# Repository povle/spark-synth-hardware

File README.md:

[![CC BY-NC-SA 4.0][cc-by-nc-sa-shield]][cc-by-nc-sa]

This work is licensed under a
[Creative Commons Attribution-NonCommercial-ShareAlike 4.0 International License][cc-by-nc-sa].

[![CC BY-NC-SA 4.0][cc-by-nc-sa-image]][cc-by-nc-sa]

[cc-by-nc-sa]: http://creativecommons.org/licenses/by-nc-sa/4.0/
[cc-by-nc-sa-image]: https://licensebuttons.net/l/by-nc-sa/4.0/88x31.png
[cc-by-nc-sa-shield]: https://img.shields.io/badge/License-CC%20BY--NC--SA%204.0-lightgrey.svg

# Spark Synth - Hardware
This repo is intended to host the hardware files and assembly information for [Spark](https://github.com/povle/spark-synth) - an open-source portable ESP32-based synth.

Important disclaimer: currently, this project is a prototype. If you really want to assemble it yourself, be prepared for a lot of drilling, sanding, double-sided-taping, soldering tiny wires and figuring stuff out on your own. You can contact [me on Reddit](https://www.reddit.com/user/Pashog/) and I might help if I have the time for that, but no guarantees here.

Moving forward I'm planning to design an easier to assemble V2 with everything mounted on custom PCBs, but I can't provide any timeline on that.

Feel free to modify and improve the design, but respect the licensing.

## Electronics - Bill of Materials
|   Component                                                                 | Function                         | **Comments**                                                                                                                                                                                                                                                                                                      |
|-----------------------------------------------------------------------------|----------------------------------|-------------------------------------------------------------------------------------------------------------------------------------------------------------------------------------------------------------------------------------------------------------------------------------------------------------------|
| ESP-32 S3 N16R8                                                             | Microcontroller                  | I've used some no-name devboard marked "S3 AI". Note the "N16R8" - the project does need a lot of PSRAM.                                                                                                                                                                                                          |
| PCM 5102A                                                                   | DAC                              |                                                                                                                                                                                                                                                                                                                   |
| PAM8403                                                                     | Amp                              |                                                                                                                                                                                                                                                                                                                   |
| RV09 (10 kOhm) (x16)                                                        | Potentiometers                   | Not sure what the exact model is, but mine are vertical with a plastic 12 mm long knurled shaft.                                                                                                                                                                                                                  |
| YANJUXING 4020 4 Ohm 3W                                                     | Speaker                          | Found it on Aliexpress. It's rectangular, 40mm x 20 mm, 14.3 mm tall. The dimensions are critical, it's a pretty tight fit.                                                                                                                                                                                       |
| Adafruit USB-C breakout board                                               | USB-C                            | Any peripheral breakout board you can find that has both power and data will do. I've used a copy of [this one](https://www.adafruit.com/product/4090). Ideally look for one with 5.1k pull-down resistors on CC1 and CC2 preinstalled, so that you are not limited to Type A - Type C cables.                    |
| TP-4056                                                                     | Battery charger                  |                                                                                                                                                                                                                                                                                                                   |
| CKCS BS01                                                                   | 5V Boost converter               | Given that it's only connected to the ESP, you probably should better look for a 3.7 - 3.3V stepdown converter and power it via the 3.3V pin directly. That should be quite a bit more efficient.                                                                                                                 |
| Custom PCB for Pots                                                         | Potentiometer wiring             | You can find the KiCad project in the repo. Not essential, you could just print a mounting plate and deadbug wire all the pots to the multiplexer, but I'm not sure how well the wires will fit, there's not a lot of space there.                                                                                |
| CD74HC4067                                                                  | Analog multiplexer for the pots  |                                                                                                                                                                                                                                                                                                                   |
| On-off switch                                                               |                                  |                                                                                                                                                                                                                                                                                                                   |
| ICS 43434                                                                   | Microphone                       | Optional, used only for the sampler.                                                                                                                                                                                                                                                                              |
| B103 10K 5Pin 16x2                                                          | Volume wheel                     | Note the 5 pins. Important if you want stereo line out.                                                                                                                                                                                                                                                           |
| TLZWLA PJ-307                                                               | 3.5 mm socket                    | Important to get a switching socket.                                                                                                                                                                                                                                                                              |
| 184x74x3.5 mm Li-ion battery (5000 mAh)                                     | Battery                          | TAKE PROPER PRECAUTIONS WHEN WORKING WITH THESE! Only use batteries with a built-in protection circuit, take extreme care not to short circuit or damage them. I've designed the whole project around these dimensions, so your battery **MUST NOT** exceed them. Carefully check the clearances during assembly. |
| Keychron Low Profile Silent Red (x28)                                       | Keyboard switches                | I think any low-profile switches with Cherry stems will work? Not sure if they are all exactly the same dimensions.                                                                                                                                                                                               |
| 1N4148 (x28)                                                                | Diodes for the keyboard matrix   |                                                                                                                                                                                                                                                                                                                   |
| MCP23017                                                                    | I2C IO Expander for the keyboard | Technically optional, i've only used it to minimize the amount of wiring between the top case and the bottom case. I think that ESP32 has enough pins left to connect the keyboard matrix directly, but that will make the wiring even more of a mess.                                                            |
| 128x64 0.96 I2C OLED                                                        | Display                          | There seem to be a lot of variants with slightly different mounting dimensions, so you might have to redesign the control panel for your specific one. Or just use double sided tape.                                                                                                                             |
| 4.5x4.5x7 mm button (x4)                                                    | Control panel buttons            | These were an afterthought. They don't feel that nice, are tiny but still barely fit. This should definitely be redesigned.                                                                                                                                                                                       |
| [GPD WIN 3 Joystick](https://www.aliexpress.com/item/1005005994714895.html) | Joystick                         | I bought this because it was the only one i could fit when i was planning to use the Korg Nanokey PCB for the keybed. Now there's a lot more space inside, so it should be doable to redesign it for something more common.                                                                                       |
| FPC 6 Pin 0.5 mm Breakout Board                                             | Breakout for the GPD joystick    |                                                                                                                                                                                                                                                                                                                   |

## Hardware - Bill of materials
| Component                      | Function                                      | Comments                                                                                                                                                                                                                                                                                                      |
| ------------------------------ | --------------------------------------------- | ------------------------------------------------------------------------------------------------------------------------------------------------------------------------------------------------------------------------------------------------------------------------------------------------------------- |
| 3D printer                     | 3D printing                                   | I've designed the project around my Bambu Lab A1 Mini, so almost any printer will be big enough.                                                                                                                                                                                                              |
| M3x6x5 Heat insert (x4)        | Connecting the case halves                    | I've screwed up (pun intended) with the top-right one, under the potentiometer recess. It pokes through the case (you can even see that in the photos). This should be redesigned. There's also a hole for a fifth heat insert in the center of the top case, but that would go straight through the battery. |
| M3x12 Screw (x4)               | Connecting the case halves                    |                                                                                                                                                                                                                                                                                                               |
| M2x2x3 Heat insert (x10)       | Connecting the keyboard plate to the top case | They are TINY. I had to screw an M2 bolt in and heat up the whole thing with a soldering iron so that no plastic gets on the threads.                                                                                                                                                                         |
| M2 Screw (x10)                 | Connecting the keyboard plate to the top case | I've had to cut them down to specific lengths so they fit...                                                                                                                                                                                                                                                  |
| eSun PLA+ White                | Structural components                         | Maybe switching to PETG would be a good idea.                                                                                                                                                                                                                                                                 |
| Bambu Lab Pla Matte (Sky Blue) | Everything blue                               |                                                                                                                                                                                                                                                                                                               |

## 3D printed parts
For now I'm providing them as a .3mf project, I will upload the .STEP files to the repo upon request (not sure if anyone will actually want to modify any of this),
### Bottom case
Consists of 3 parts: bottom_left, bottom_right, bottom_dovetail. I've used a lot of CA glue to connect them.
No supports needed, default 15% infill settings
 seem fine.

You will note that it's just a plain tub with no attachments for the components. I've printed it as a prototype to check how all my components and wires fit IRL and just stuck with it, using double-sided tape for securing most components. For the ones that need a stronger connection I've either hand drilled holes for M2 screws or used CA glue.

I'm sure I could do a much better job with wire management here, but I'm not touching this with a 10-foot pole until something breaks.

There are mounting holes for an IO side panel, but I still haven't designed one.

Some of the bottom screw holes are slightly wrong, because the version of the bottom case was designed for a different iteration of the top case. Can be fixed with a drill.

### Keyboard mounting plate
Consists of two independent parts: keyboard_left and keyboard_right. They are not initially attached to each other, both will be held in place when connected to the top case. After that you can glue them together with the connecting plate.

Note that the switches are attached sideways for better stability and easier wiring.

### Top case

This is the most complicated part of the build. The main part of it consists of two halves glued together with a thin dovetail plate. The control panel is simply held in with friction, you could add a dab of glue if needed.

The keys are wired in a 5x6 matrix with the rows and the columns connected to an IO expander. I've made traces using copper tape thinking that it would make the wiring cleaner. I really don't think that it did. I would advise to just use thin wire.

The buttons are wired directly to the 5 remaining pins on the expander. They are mounted on a screwed-in piece of perfboard.

I've printed thin covers so that the keyboard doesn't get shorted with something in the bottom case.

A lot of small glued-in decorative parts, should be mostly obvious. There's a separate white part glued on the pot panel for better surface quality. I've colored the space under the letters with a black sharpie and then glued the labels on. The labels were printed with a 0.2 mm nozzle, not sure if you could resolve them with a 0.4 mm.

The joystick knob is 3d printed, with a silicone cover made for Switch 2.

## Conclusion
Hope that this was useful or at least interesting. TERRIBLY SORRY for a lot of my design (in)decisions to anyone who might have decided to build this. Stay tuned for V2! Should be significantly friendlier to DIY.

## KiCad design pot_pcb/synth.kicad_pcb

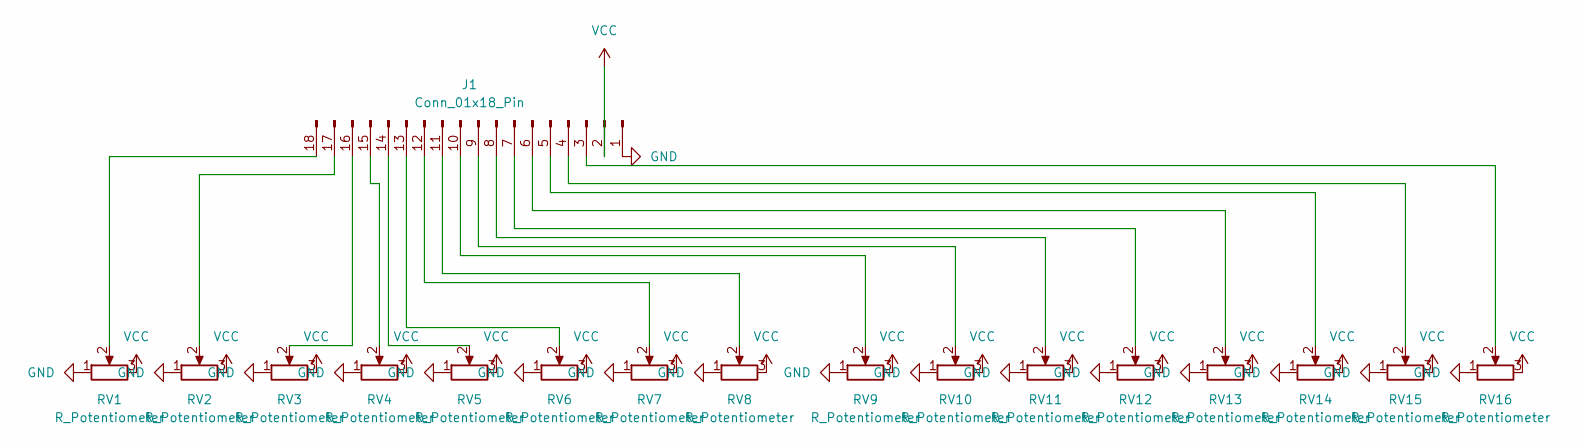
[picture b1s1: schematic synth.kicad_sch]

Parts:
J1: Conn_01x18_Pin; PinHeader_1x18_P2.54mm_Vertical
RV1, RV2, RV3, RV4, RV5, RV6, RV7, RV8, RV9, RV10, RV11, RV12, RV13, RV14, RV15, RV16: R_Potentiometer; Potentiometer_Alps_RK09K_Single_Vertical

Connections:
GND: J1.1, RV1.1, RV1.MP, RV2.1, RV2.MP, RV3.1, RV3.MP, RV4.1, RV4.MP, RV5.1, RV5.MP, RV6.1, RV6.MP, RV7.1, RV7.MP, RV8.1, RV8.MP, RV9.1, RV9.MP, RV10.1, RV10.MP, RV11.1, RV11.MP, RV12.1, RV12.MP, RV13.1, RV13.MP, RV14.1, RV14.MP, RV15.1, RV15.MP, RV16.1, RV16.MP
unnamed: J1.3, RV16.2
unnamed: J1.4, RV15.2
unnamed: J1.5, RV14.2
unnamed: J1.6, RV13.2
unnamed: J1.7, RV12.2
unnamed: J1.8, RV11.2
unnamed: J1.9, RV10.2
unnamed: J1.10, RV9.2
unnamed: J1.11, RV8.2
unnamed: J1.12, RV7.2
unnamed: J1.13, RV6.2
unnamed: J1.14, RV5.2
unnamed: J1.15, RV4.2
unnamed: J1.16, RV3.2
unnamed: J1.17, RV2.2
unnamed: J1.18, RV1.2
VCC: J1.2, RV1.3, RV2.3, RV3.3, RV4.3, RV5.3, RV6.3, RV7.3, RV8.3, RV9.3, RV10.3, RV11.3, RV12.3, RV13.3, RV14.3, RV15.3, RV16.3

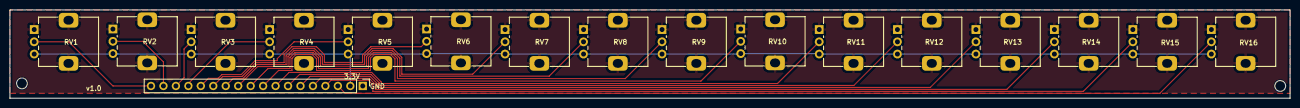
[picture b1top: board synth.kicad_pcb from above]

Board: 2 copper layers, 261.0 x 18.0 mm, 19 parts (0 on the bottom side), 18 nets.

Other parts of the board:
 : MountingHole_2.2mm_M2_DIN965
 #2: MountingHole_2.2mm_M2_DIN965
